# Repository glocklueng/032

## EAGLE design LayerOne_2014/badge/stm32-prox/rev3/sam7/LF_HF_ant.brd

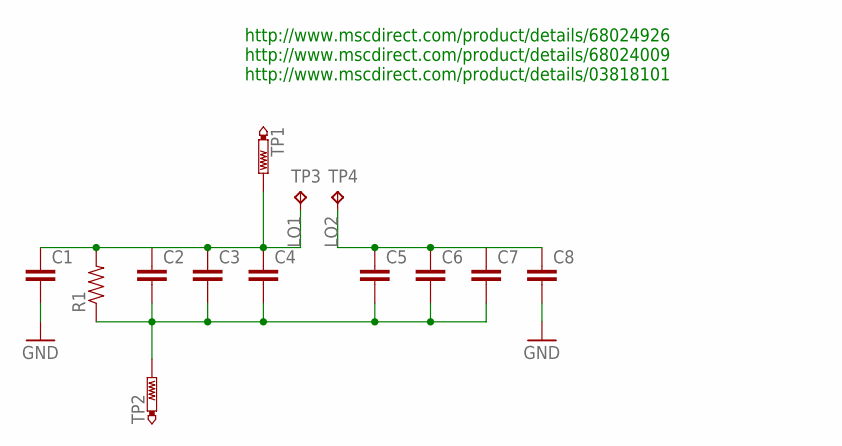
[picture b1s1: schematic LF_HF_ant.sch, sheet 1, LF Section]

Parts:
C1, C2, C3, C4, C5, C6, C7, C8: CAP1206; 1206
R1: RESISTOR0603-RES; 0603-RES
TP1, TP2: PTR1PAD1-17; P1-17
TP3, TP4: TP; TP_MILLMAX_R

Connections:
GND: C1.2, C8.2; also elsewhere on the board
LO1: C1.1, C2.1, C3.1, C4.1, R1.2, TP1.TP, TP3.TP; also elsewhere on the board
LO2: C5.1, C6.1, C7.1, C8.1, TP4.TP; also elsewhere on the board
unnamed: C2.2, C3.2, C4.2, C5.2, C6.2, C7.2, R1.1, TP2.TP

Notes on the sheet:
http://www.mscdirect.com/product/details/68024926 http://www.mscdirect.com/product/details/68024009 http://www.mscdirect.com/product/details/03818101

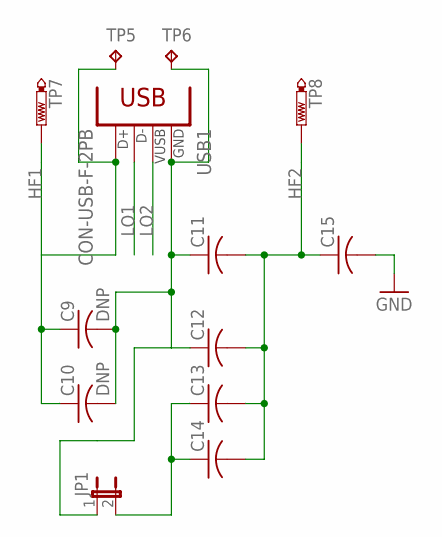
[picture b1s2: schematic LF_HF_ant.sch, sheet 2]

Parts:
C9, C10: DNP; C1206
C11, C12, C13, C14, C15: C-USC1206; C1206
JP1: JUMPER-2SMD-NO; SJ_2S-NO
TP5, TP6: TP; TP_MILLMAX_R
TP7, TP8: PTR1PAD1-17; P1-17
USB1: CON-USB-F-2PB; CONN_USB_A_F

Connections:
GND: C15.2; also elsewhere on the board
HF1: C9.1, C10.1, TP5.TP, TP7.TP, USB1.3 (D+)
HF2: C11.2, C12.2, C13.2, C14.2, C15.1, TP8.TP
LO1: USB1.2 (D-); also elsewhere on the board
LO2: USB1.1 (VUSB); also elsewhere on the board
unnamed: C9.2, C10.2, C11.1, C12.1, JP1.1, TP6.TP, USB1.4 (GND)
unnamed: C13.1, C14.1, JP1.2

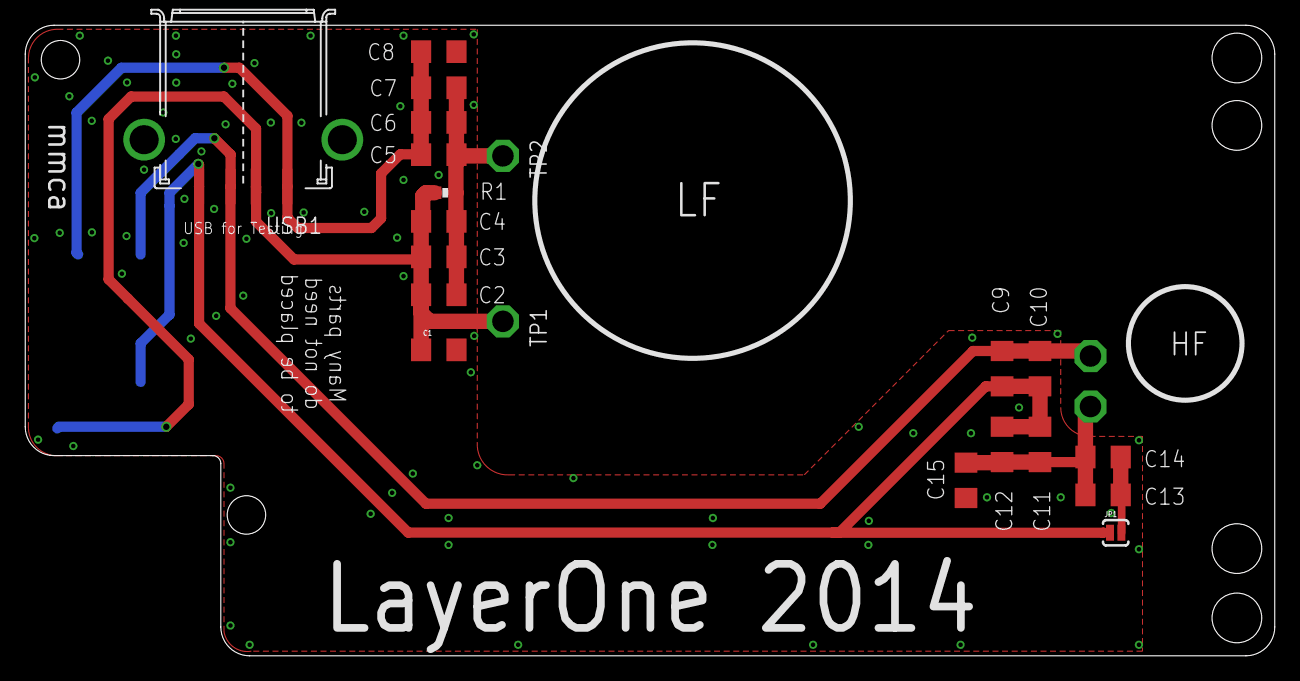
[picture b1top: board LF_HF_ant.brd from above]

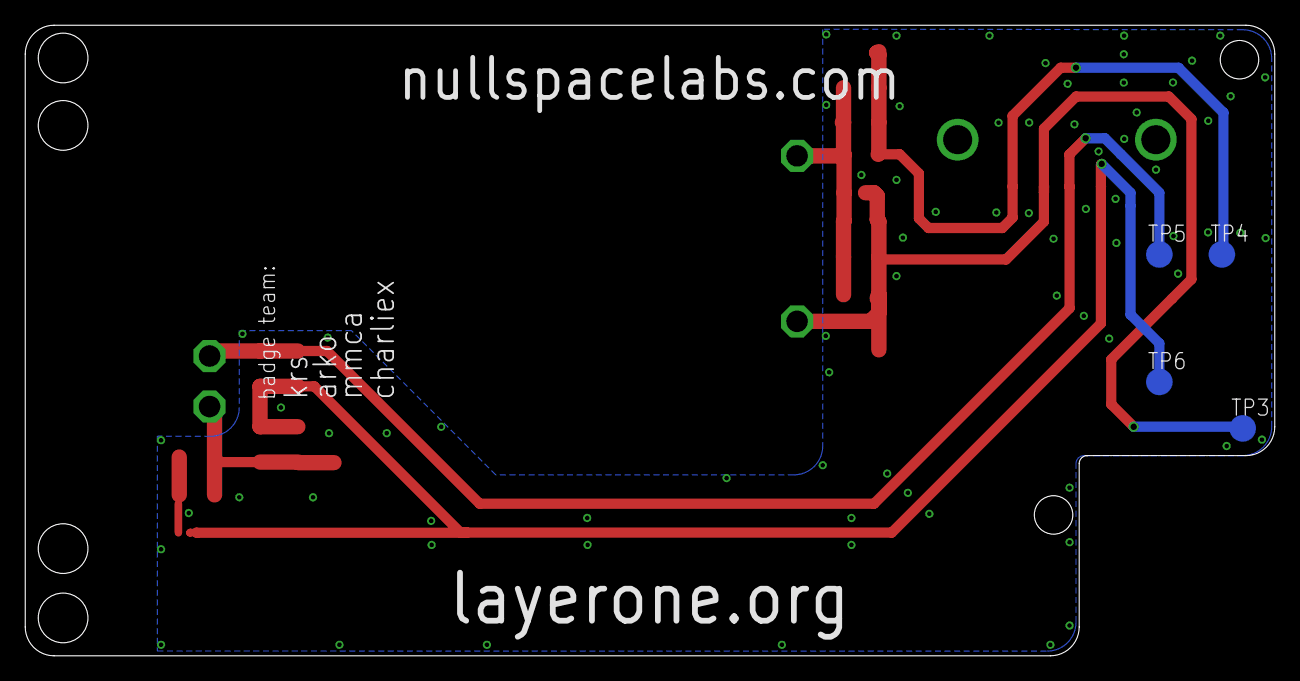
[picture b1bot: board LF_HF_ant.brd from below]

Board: 2 copper layers, 99.0 x 50.0 mm, 30 parts (5 on the bottom side), 8 nets.

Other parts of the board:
U$1, U$2: STM32-PROX_L1LOGO
U$3, U$4: STAND-OFF-TIGHT

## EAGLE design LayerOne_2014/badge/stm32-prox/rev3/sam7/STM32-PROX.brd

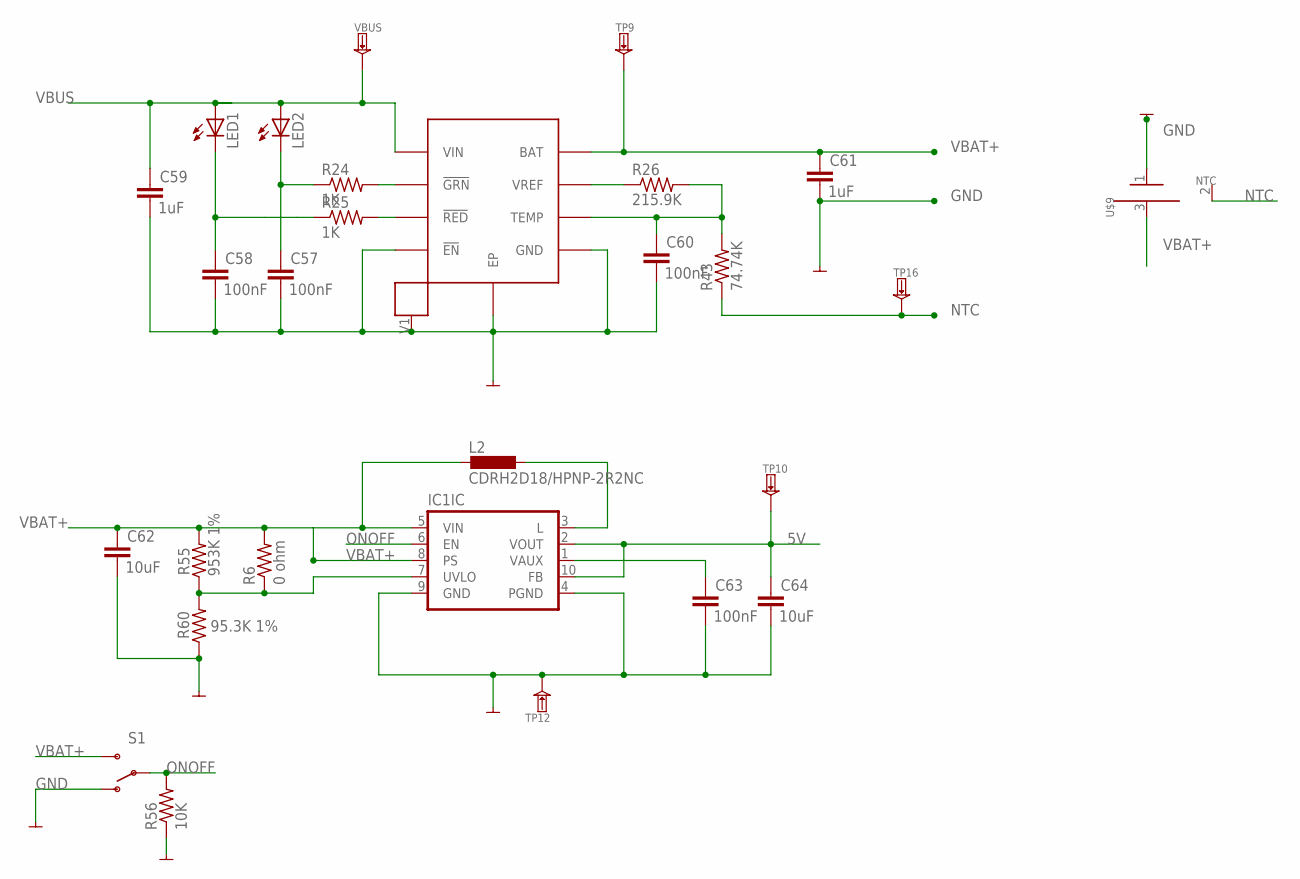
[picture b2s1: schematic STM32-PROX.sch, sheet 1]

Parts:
C57, C58, C60, C63: 100nF; RLC_0603; MPN CL10B104KO8NNNC; DIGIKEY 1276-1005-1-ND
C59, C61: 1uF; RLC_0603; MPN CC0603ZRY5V7BB105; DIGIKEY 311-1372-2-ND
C62, C64: 10uF; RLC_0603; MPN C1608X5R1C106M080AB; DIGIKEY 445-9065-1-ND
IC1: IC_TPS6120XQFN10; QFN-10; MPN TPS61202DRCT; DIGIKEY 296-21685-1-ND
L2: CDRH2D18/HPNP-2R2NC; CDRH2D18; MPN CDRH2D18/HPNP-2R2NC; DIGIKEY 308-2295-1-ND
LED1: LED_LEDSML0603; LED_SML0603; PARTNO *; DIGIKEY 475-1409-1-ND
LED2: LED_LEDSML0603; LED_SML0603; PARTNO *; DIGIKEY 475-3016-1-ND
R6: 0 ohm; RLC_0603; MPN RMCF0603JT1K00; DIGIKEY RMCF0603JT1K00TR-ND
R24, R25: 1K; RLC_0603; MPN RMCF0603JT1K00; DIGIKEY RMCF0603JT1K00TR-ND
R26: 215.9K; RLC_0603; MPN CRCW0603215KFKEA; DIGIKEY 541-215KHCT-ND
R43: 74.74K; RLC_0603; MPN RMCF0603JT75K0; DIGIKEY RMCF0603JT75K0CT-ND
R55: 953K 1%; RLC_0603; TOLERANCE 5%; MPN RC0603FR-07953KL; DIGIKEY 311-953KHRCT-ND
R56: 10K; RLC_0603; MPN RMCF0603JT1K00; DIGIKEY RMCF0603JT1K00TR-ND
R60: 95.3K 1%; RLC_0603; TOLERANCE 1%; MPN RC0603FR-0795K3L; DIGIKEY 311-95.3KHRCT-ND
S1: SWITCH-SPDT-SMD-A; SWITCH-SPST-SMD-A; PARTNO *
TP9, TP10: TESTPADKEYSTONE-SMD; --MERGED_KEYSTONE-SMD-TESTPOINT-5015; MPN NONE
TP12: TESTPADKEYSTONE-PTH; KEYSTONE-PTH-TESTPOINT-5011; MPN NONE
TP16: TESTPAD; SMD-TESTPOINT; PARTNO NONE
U$7: MC34674; UDFN-EP; MPN MC34674AEPR2; DIGIKEY MC34674AEPR2TR-ND
U$9: BATT; MPN MC34674AEPR2; DIGIKEY MC34674AEPR2TR-ND
VBUS: TESTPADKEYSTONE-PTH; KEYSTONE-PTH-TESTPOINT-5011; MPN NONE

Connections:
5V: C64.1, IC1.2 (VOUT), IC1.10 (FB), TP10.1; also elsewhere on the board
unnamed: C57.1, LED2.C, R24.1
unnamed: R24.2, U$7.2 (!GRN)
unnamed: C58.1, LED1.C, R25.1
unnamed: R25.2, U$7.3 (!RED)
unnamed: R26.1, U$7.7 (VREF)
unnamed: C60.1, R26.2, R43.2, U$7.6 (TEMP)
unnamed: C63.1, IC1.1 (VAUX)
unnamed 119: IC1.7 (UVLO), R6.1, R55.1, R60.2; also elsewhere on the board
unnamed: IC1.3 (L), L2.P$2 (2)
NTC: R43.1, TP16.1, U$9.2 (NTC)
ONOFF: IC1.6 (EN), R56.2, S1.2
VBUS: C59.1, LED1.A, LED2.A, U$7.1 (VIN), VBUS.A; also elsewhere on the board

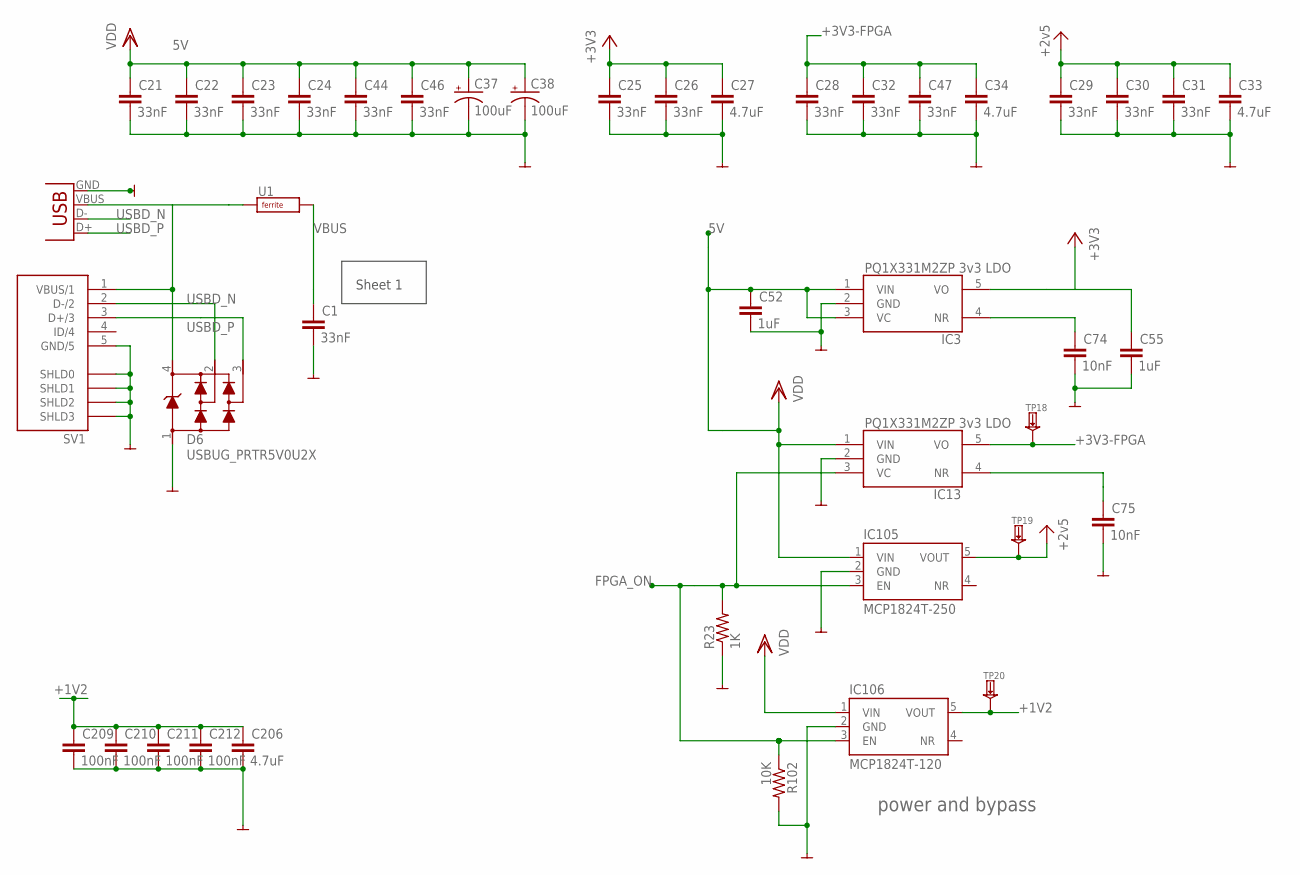
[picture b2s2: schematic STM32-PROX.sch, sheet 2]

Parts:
C1, C21, C22, C23, C24, C25, C26, C28, C29, C30, C31, C32, C44, C46, C47: 33nF; RLC_0603; MPN CC0603KRX7R9BB333; DIGIKEY 311-1429-1-ND
C27, C33, C34: 4.7uF; RLC_1210; MPN CL32B475KOINNNE; DIGIKEY 1276-1856-1-ND
C37, C38: 100uF; D/7343-31R; MPN T491D107K010AT; DIGIKEY 399-3769-1-ND
C52, C55: 1uF; RLC_0603; MPN CC0603KRX7R9BB333; DIGIKEY 311-1429-1-ND
C74, C75: 10nF; RLC_0603; MPN C0603C103K5RACTU; DIGIKEY 399-1091-2-ND
C206: 4.7uF; RLC_0603; MPN CL10A475KO8NNNC; DIGIKEY 1276-1784-2-ND
C209, C210, C211, C212: 100nF; RLC_0603; MPN CL10B104KO8NNNC; DIGIKEY 1276-1005-1-ND
D6: USBUG_PRTR5V0U2X; USBUG_SOT143B; MPN PRTR5V0U2X,215; DIGIKEY 568-4140-1-ND
IC3: PQ1X331M2ZP-3V3-LDO-SOT-23-5; SOT-23-5; MPN LP2985-33DBVR; DIGIKEY 296-18476-1-ND
IC13: PQ1X331M2ZP-3V3-LDO-SOT-23-5; SOT-23-5; MPN LP2985-33DBVR; DIGIKEY 296-18476-2-ND
IC105: MCP1824T-250; SOT-23-5; MPN MCP1824T-2502E/OT; DIGIKEY MCP1824T-2502E/OTCT-ND
IC106: MCP1824T-120; SOT-23-5; MPN MCP1824T-1202E/OT; DIGIKEY MCP1824T-1202E/OTCT-ND
R23: 1K; RLC_0603; MPN RMCF0603JT1K00; DIGIKEY RMCF0603JT1K00CT-ND
R102: 10K; RLC_0603; MPN RMCF0603JT10K0; DIGIKEY RMCF0603JT10K0CT-ND
SV1: USB-MINIB; USB-MINIB-SMD; PARTNO *
TP18, TP19, TP20: TESTPAD; SMD-TESTPOINT; PARTNO NONE
U1: FERRITE0805; RLC_0805; MPN MPZ2012S300A; DIGIKEY 445-1566-1-ND
USB-MICRO: USB-MICROB; MPN 1981568-1; DIGIKEY A97800CT-ND

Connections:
5V: C21.1, C22.1, C23.1, C24.1, C37.+, C38.+, C44.1, C46.1, C52.1, IC3.1 (VIN), IC3.3 (VC), IC13.1 (VIN), IC105.1 (VIN), IC106.1 (VIN); also elsewhere on the board
+1V2: C206.1, C209.1, C210.1, C211.1, C212.1, IC106.5 (VOUT), TP20.1; also elsewhere on the board
+2V5: C29.1, C30.1, C31.1, C33.1, IC105.5 (VOUT), TP19.1; also elsewhere on the board
+3V3-FPGA: C28.1, C32.1, C34.1, C47.1, IC13.5 (VO), TP18.1; also elsewhere on the board
FPGA_ON: IC13.3 (VC), IC105.3 (EN), IC106.3 (EN), R23.2, R102.1; also elsewhere on the board
unnamed: C74.1, IC3.4 (NR)
unnamed: C75.1, IC13.4 (NR)
USBD_N: D6.2, SV1.2 (D-/2), USB-MICRO.D-; also elsewhere on the board
USBD_P: D6.3, SV1.3 (D+/3), USB-MICRO.D+; also elsewhere on the board
VBUS: C1.1, U1.2 (B); also elsewhere on the board

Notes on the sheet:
power and bypass
Sheet 1

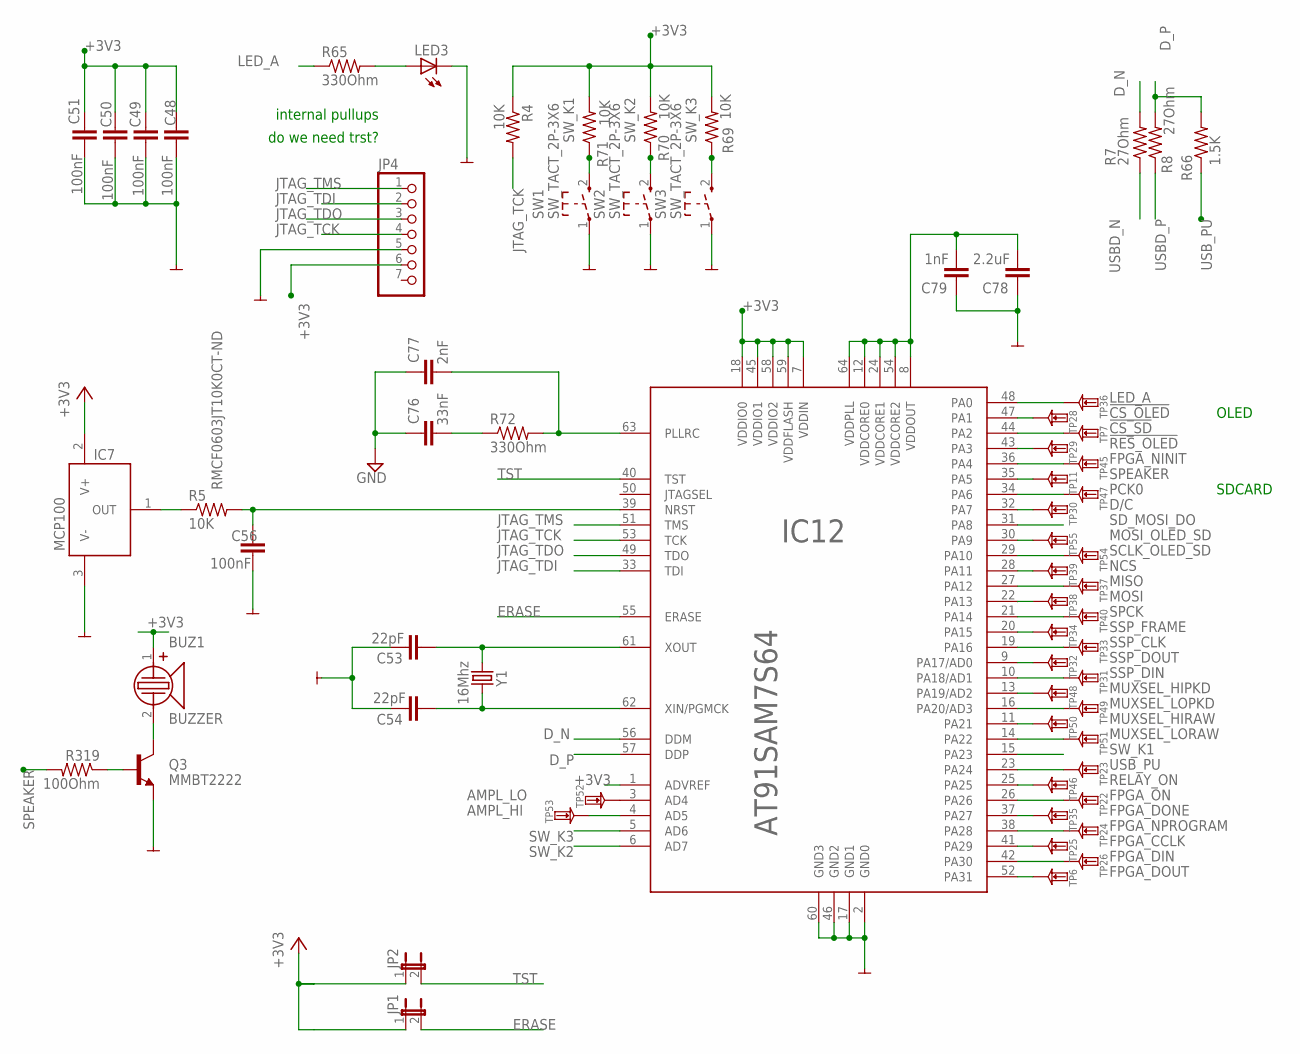
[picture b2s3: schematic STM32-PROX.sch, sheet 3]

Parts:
BUZ1: BUZZER; MPN CCV-084B16-SMT; DIGIKEY 102-1265-2-ND
C48, C49, C50, C51, C56: 100nF; RLC_0603; MPN CL10B104KO8NNNC; DIGIKEY 1276-1005-1-ND
C53, C54: 22pF; RLC_0603; MPN C1608C0G1H220J080AA; DIGIKEY 445-1273-1-ND
C76: 33nF; RLC_0603; MPN CC0603KRX7R9BB333; DIGIKEY 311-1429-1-ND
C77: 2nF; RLC_0603; MPN GRM1885C1H202JA01D; DIGIKEY 490-1458-2-ND
C78: 2.2uF; RLC_0603; MPN LMK107BJ225KA-T; DIGIKEY 587-1253-1-ND
C79: 1nF; RLC_0603; PARTNO GRM188R71H102KA01D; DIGIKEY 490-1494-2-ND
IC7: MCP100; SOT23-3LEAD; MPN MCP100T-270I/TT; DIGIKEY MCP100T-270I/TTCT-ND
IC12: AT91SAM7S512B; LQFP-64; PARTNO AT91SAM7S512B-AU; DIGIKEY AT91SAM7S512B-AU-ND
JP1, JP2: JUMPER-2PTH; 1X02
JP4: HEADER-1X7ROUND; 1X07_ROUND
LED3: LED_LEDSML0603; LED_SML0603; PARTNO *; DIGIKEY 475-2558-1-ND
Q3: MMBT2222; SOT-23-3; MPN MMBT2222A-7-F; DIGIKEY MMBT2222A-FDITR-ND
R4, R5, R69, R70, R71: 10K; RLC_0603; MPN RMCF0603JT10K0; DIGIKEY RMCF0603JT10K0CT-ND
R7, R8: 27Ohm; RLC_0603; MPN RMCF0603JT27R0; DIGIKEY RMCF0603JT27R0CT-ND
R65, R72: 330Ohm; RLC_0603; MPN RMCF0603JT330R; DIGIKEY RMCF0603JT330RCT-ND
R66: 1.5K; RLC_0603; MPN MCR03ERTJ152; DIGIKEY RHM1.5KCGTR-ND
R319: 100Ohm; RLC_0603; MPN RMCF0603JT100R; DIGIKEY RMCF0603JT100RCT-ND
SW1, SW2, SW3: SW_TACT_2P-3X6; SW_TACT_3X6
TP6, TP7, TP11, TP22, TP23, TP24, TP25, TP26, TP28, TP29, TP30, TP31, TP32, TP33, TP34, TP35, TP36, TP37, TP38, TP39, TP40, TP45, TP46, TP47, TP48, TP49, TP50, TP51, TP52, TP53, TP54, TP55: TESTPAD; SMD-TESTPOINT; PARTNO NONE
Y1: 16Mhz; CRYSTAL-TXC-7A; MPN 7A-16.000MAAJ-T; DIGIKEY 887-1086-1-ND

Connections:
!CS_OLED: IC12.47 (PA1), TP28.1; also elsewhere on the board
!CS_SD: IC12.44 (PA2), TP7.1; also elsewhere on the board
!RES_OLED: IC12.43 (PA3), TP29.1; also elsewhere on the board
AMPL_HI: IC12.4 (AD5), TP53.1; also elsewhere on the board
AMPL_LO: IC12.3 (AD4), TP52.1; also elsewhere on the board
D/C: IC12.32 (PA7), TP30.1; also elsewhere on the board
D_N: IC12.56 (DDM), R7.2
D_P: IC12.57 (DDP), R8.2, R66.2
FPGA_CCLK: IC12.41 (PA29), TP25.1; also elsewhere on the board
FPGA_DIN: IC12.42 (PA30), TP26.1; also elsewhere on the board
FPGA_DONE: IC12.37 (PA27), TP35.1; also elsewhere on the board
FPGA_DOUT: IC12.52 (PA31), TP6.1; also elsewhere on the board
FPGA_NINIT: IC12.36 (PA4), TP45.1; also elsewhere on the board
FPGA_NPROGRAM: IC12.38 (PA28), TP24.1; also elsewhere on the board
FPGA_ON: IC12.26 (PA26), TP22.1; also elsewhere on the board
JTAG_TCK: IC12.53 (TCK), JP4.4, R4.2
JTAG_TDI: IC12.33 (TDI), JP4.2
JTAG_TDO: IC12.49 (TDO), JP4.3
JTAG_TMS: IC12.51 (TMS), JP4.1
LED3: LED3.A, R65.2
LED_A: IC12.48 (PA0), R65.1, TP36.1
MISO: IC12.27 (PA12), TP37.1; also elsewhere on the board
MOSI: IC12.22 (PA13), TP38.1; also elsewhere on the board
MOSI_OLED_SD: IC12.30 (PA9), TP55.1; also elsewhere on the board
MUXSEL_HIPKD: IC12.13 (PA19/AD2), TP48.1; also elsewhere on the board
MUXSEL_HIRAW: IC12.11 (PA21), TP50.1; also elsewhere on the board
MUXSEL_LOPKD: IC12.16 (PA20/AD3), TP49.1; also elsewhere on the board
MUXSEL_LORAW: IC12.14 (PA22), TP51.1; also elsewhere on the board
unnamed: C53.2, IC12.61 (XOUT), Y1.P$1 (1)
unnamed: BUZ1.2, Q3.3 (C)
unnamed: Q3.1 (B), R319.1
unnamed: C54.2, IC12.62 (XIN/PGMCK), Y1.P$2 (2)
unnamed: IC7.1 (OUT), R5.1
unnamed: C78.2, C79.2, IC12.8 (VDDOUT), IC12.12 (VDDCORE0), IC12.24 (VDDCORE1), IC12.54 (VDDCORE2), IC12.64 (VDDPLL)
unnamed: C77.2, IC12.63 (PLLRC), R72.2
unnamed: C76.2, R72.1
NCS: IC12.28 (PA11), TP39.1; also elsewhere on the board
NRST: C56.1, IC12.39 (NRST), R5.2
unnamed: IC12.55 (ERASE), JP1.2
PCK0: IC12.34 (PA6), TP47.1; also elsewhere on the board
RELAY_ON: IC12.25 (PA25), TP46.1; also elsewhere on the board
SCLK_OLED_SD: IC12.29 (PA10), TP54.1; also elsewhere on the board
SD_MOSI_DO: IC12.31 (PA8); also elsewhere on the board
SPCK: IC12.21 (PA14), TP40.1; also elsewhere on the board
SPEAKER: IC12.35 (PA5), R319.2, TP11.1
SSP_CLK: IC12.19 (PA16), TP33.1; also elsewhere on the board
SSP_DIN: IC12.10 (PA18/AD1), TP31.1; also elsewhere on the board
SSP_DOUT: IC12.9 (PA17/AD0), TP32.1; also elsewhere on the board
SSP_FRAME: IC12.20 (PA15), TP34.1; also elsewhere on the board
SW_K1: IC12.15 (PA23), R71.1, SW1.2 (3); also elsewhere on the board
SW_K2: IC12.6 (AD7), R70.1, SW2.2 (3); also elsewhere on the board
SW_K3: IC12.5 (AD6), R69.1, SW3.2 (3); also elsewhere on the board
USBD_N: R7.1; also elsewhere on the board
USBD_P: R8.1; also elsewhere on the board
USB_PU: IC12.23 (PA24), R66.1, TP23.1

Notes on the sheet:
do we need trst?
internal pullups
OLED
SDCARD

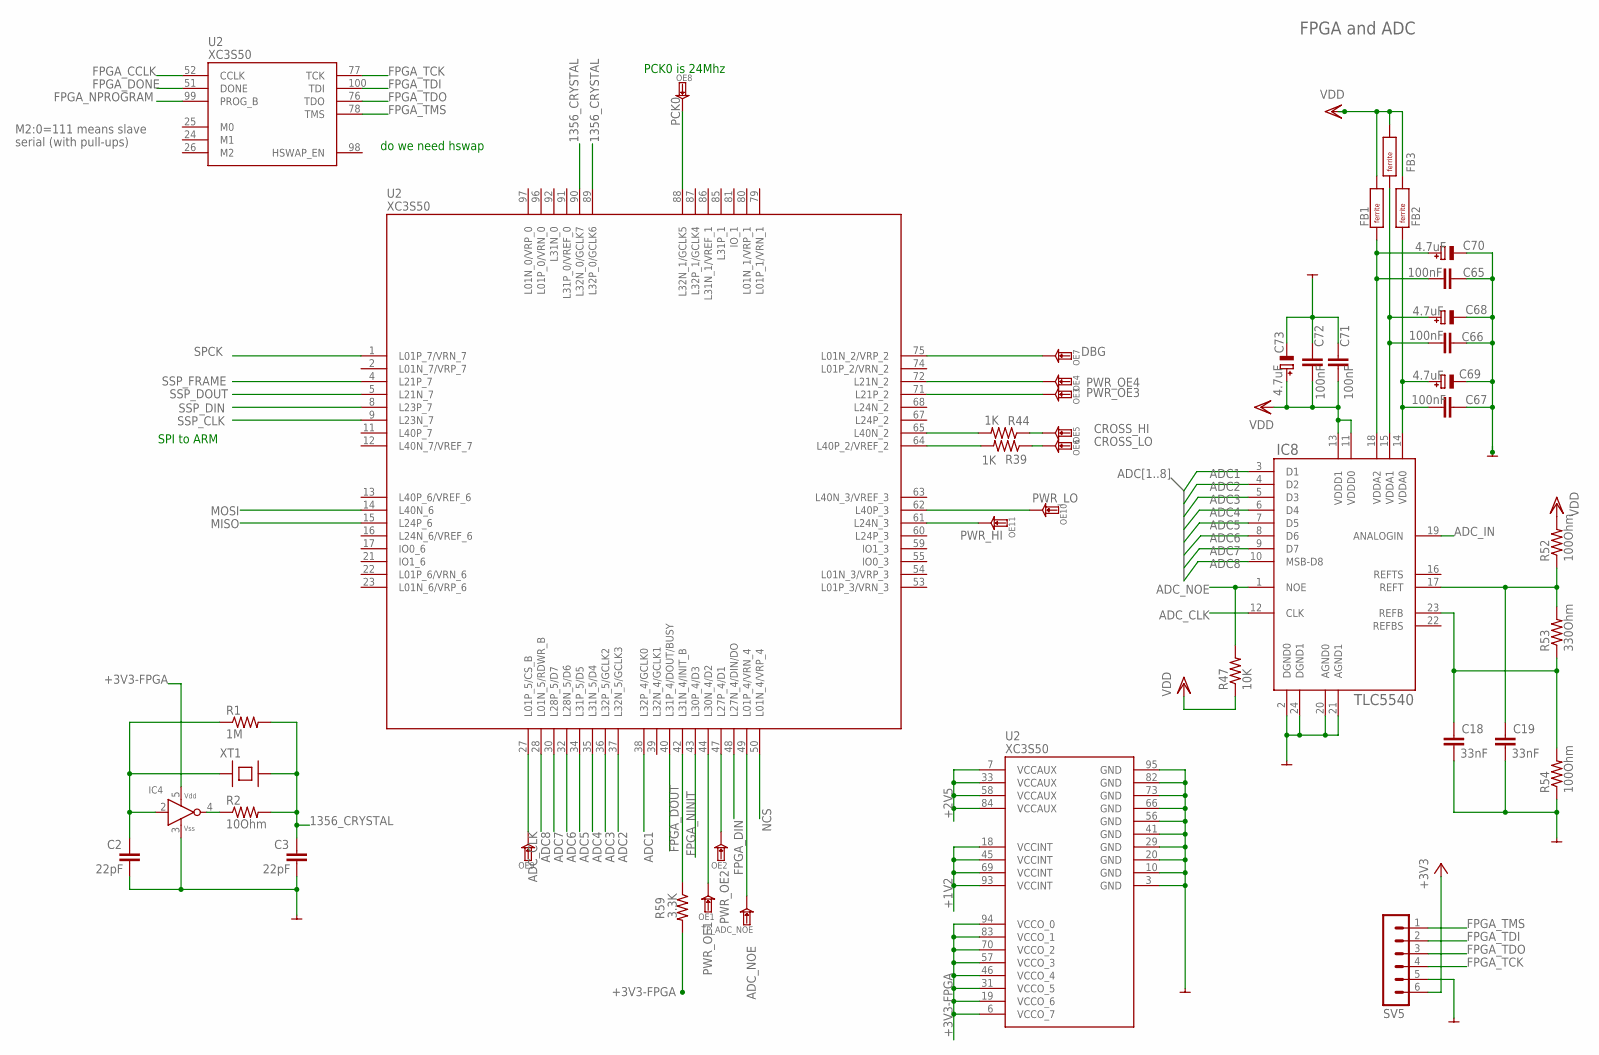
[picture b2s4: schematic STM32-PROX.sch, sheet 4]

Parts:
C2, C3: 22pF; RLC_0603; MPN C1608C0G1H220J080AA; DIGIKEY 445-1273-1-ND
C18, C19: 33nF; RLC_0603; MPN CC0603KRX7R9BB333; DIGIKEY 311-1429-1-ND
C65, C66, C67, C71, C72: 100nF; RLC_0603; MPN CL10B104KO8NNNC; DIGIKEY 1276-1005-1-ND
C68, C69, C70, C73: 4.7uF; EIA3216-18/A-R; PARTNO T491A475M010AT; DIGIKEY 399-3698-1-ND
FB1, FB2, FB3: 600 OHM; RLC_0603; PARTNO CIM10J601NC; DIGIKEY 1276-6379-2-ND
IC4: HCU-INVERTER; SMV-5; MPN NC7SZ04M5X; DIGIKEY NC7SZ04M5XCT-ND
IC8: TLC5540; TSSOP-24; MPN TLC5540IPW; DIGIKEY 296-2184-5-ND
OE1, OE2, OE3, OE4, OE5, OE6, OE7, OE8, OE9, OE10, OE11: TESTPAD; SMD-TESTPOINT; PARTNO NONE
R1: 1M; RLC_0603; MPN RC0603JR-071ML; DIGIKEY 311-1.0MGRTR-ND
R2: 10Ohm; RLC_0603; MPN RMCF0603JT100R; DIGIKEY RMCF0603JT100RCT-ND
R39, R44: 1K; RLC_0603; MPN RMCF0603JT1K00; DIGIKEY RMCF0603JT1K00CT-ND
R47: 10K; RLC_0603; MPN RMCF0603JT10K0; DIGIKEY RMCF0603JT10K0CT-ND
R52, R54: 100Ohm; RLC_0603; MPN RMCF0603JT100R; DIGIKEY RMCF0603JT100RCT-ND
R53: 330Ohm; RLC_0603; MPN RMCF0603JT330R; DIGIKEY RMCF0603JT330RCT-ND
R59: 3.3K; RLC_0603; MPN RMCF0603JT3K30; DIGIKEY RMCF0603JT3K30CT-ND
SV5: HEADER-MALE-6X1; HEADER-MALE-6X1-0.100-UNKEYED; PARTNO *
TP_ADC_NOE: TESTPAD; SMD-TESTPOINT; PARTNO NONE
U2: XC3S50; VQ100; MPN XC3S50-5VQ100C (not on bom)
XT1: XTAL-SMD-CITIZEN-CS10; MPN ABM3-13.560MHZ-B2-T; DIGIKEY 535-9101-1-ND

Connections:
5V: C71.1, C72.1, C73.+, FB1.2 (B), FB2.2 (B), FB3.2 (B), IC8.11 (VDDD0), IC8.13 (VDDD1), R47.1, R52.2; also elsewhere on the board
1356_CRYSTAL: C3.1, R1.2, R2.2, U2.89 (L32P_0/GCLK6), U2.90 (L32N_0/GCLK7), XT1.B
+1V2: U2.18 (VCCINT), U2.45 (VCCINT), U2.69 (VCCINT), U2.93 (VCCINT); also elsewhere on the board
+2V5: U2.7 (VCCAUX), U2.33 (VCCAUX), U2.58 (VCCAUX), U2.84 (VCCAUX); also elsewhere on the board
+3V3-FPGA: IC4.5 (VDD), R59.2, U2.6 (VCCO_7), U2.19 (VCCO_6), U2.31 (VCCO_5), U2.46 (VCCO_4), U2.57 (VCCO_3), U2.70 (VCCO_2), U2.83 (VCCO_1), U2.94 (VCCO_0); also elsewhere on the board
ADC1: IC8.3 (D1), U2.38 (L32P_4/GCLK0)
ADC2: IC8.4 (D2), U2.37 (L32N_5/GCLK3)
ADC3: IC8.5 (D3), U2.36 (L32P_5/GCLK2)
ADC4: IC8.6 (D4), U2.35 (L31N_5/D4)
ADC5: IC8.7 (D5), U2.34 (L31P_5/D5)
ADC6: IC8.8 (D6), U2.32 (L28N_5/D6)
ADC7: IC8.9 (D7), U2.30 (L28P_5/D7)
ADC8: IC8.10 (MSB-D8), U2.28 (L01N_5/RDWR_B)
ADC_CLK: IC8.12 (CLK), OE9.1, U2.27 (L01P_5/CS_B)
ADC_IN: IC8.19 (ANALOGIN); also elsewhere on the board
ADC_NOE: IC8.1 (NOE), R47.2, TP_ADC_NOE.1, U2.49 (L01P_4/VRN_4)
CROSS_HI: OE5.1, R44.1; also elsewhere on the board
CROSS_LO: OE6.1, R39.1; also elsewhere on the board
DBG: OE7.1, U2.75 (L01N_2/VRP_2)
FPGA_CCLK: U2.52 (CCLK); also elsewhere on the board
FPGA_DIN: U2.48 (L27N_4/DIN/DO); also elsewhere on the board
FPGA_DONE: U2.51 (DONE); also elsewhere on the board
FPGA_DOUT: U2.40 (L31P_4/DOUT/BUSY); also elsewhere on the board
FPGA_NINIT: R59.1, U2.42 (L31N_4/INIT_B); also elsewhere on the board
FPGA_NPROGRAM: U2.99 (PROG_B); also elsewhere on the board
FPGA_TCK: SV5.4, U2.77 (TCK)
FPGA_TDI: SV5.2, U2.100 (TDI)
FPGA_TDO: SV5.3, U2.76 (TDO)
FPGA_TMS: SV5.1, U2.78 (TMS)
MISO: U2.15 (L24P_6); also elsewhere on the board
MOSI: U2.14 (L40N_6); also elsewhere on the board
unnamed: IC4.4 (Y), R2.1
unnamed: C2.1, IC4.2 (A), R1.1, XT1.A
unnamed: C18.1, IC8.23 (REFB), R53.1, R54.2
unnamed: R39.2, U2.64 (L40P_2/VREF_2)
unnamed: C67.1, C69.+, FB2.1 (A), IC8.14 (VDDA0)
unnamed: C66.1, C68.+, FB3.1 (A), IC8.15 (VDDA1)
unnamed: C65.1, C70.+, FB1.1 (A), IC8.18 (VDDA2)
unnamed: R44.2, U2.65 (L40N_2)
unnamed: C19.1, IC8.17 (REFT), R52.1, R53.2
NCS: U2.50 (L01N_4/VRP_4); also elsewhere on the board
PCK0: OE8.1, U2.88 (L32N_1/GCLK5); also elsewhere on the board
PWR_HI: OE11.1, U2.61 (L24N_3); also elsewhere on the board
PWR_LO: OE10.1, U2.62 (L40P_3); also elsewhere on the board
PWR_OE1: OE1.1, U2.44 (L30N_4/D2); also elsewhere on the board
PWR_OE2: OE2.1, U2.47 (L27P_4/D1); also elsewhere on the board
PWR_OE3: OE3.1, U2.71 (L21P_2); also elsewhere on the board
PWR_OE4: OE4.1, U2.72 (L21N_2); also elsewhere on the board
SPCK: U2.1 (L01P_7/VRN_7); also elsewhere on the board
SSP_CLK: U2.9 (L23N_7); also elsewhere on the board
SSP_DIN: U2.8 (L23P_7); also elsewhere on the board
SSP_DOUT: U2.5 (L21N_7); also elsewhere on the board
SSP_FRAME: U2.4 (L21P_7); also elsewhere on the board

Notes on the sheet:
FPGA and ADC
M2:0=111 means slave
serial (with pull-ups)
do we need hswap
PCK0 is 24Mhz
SPI to ARM

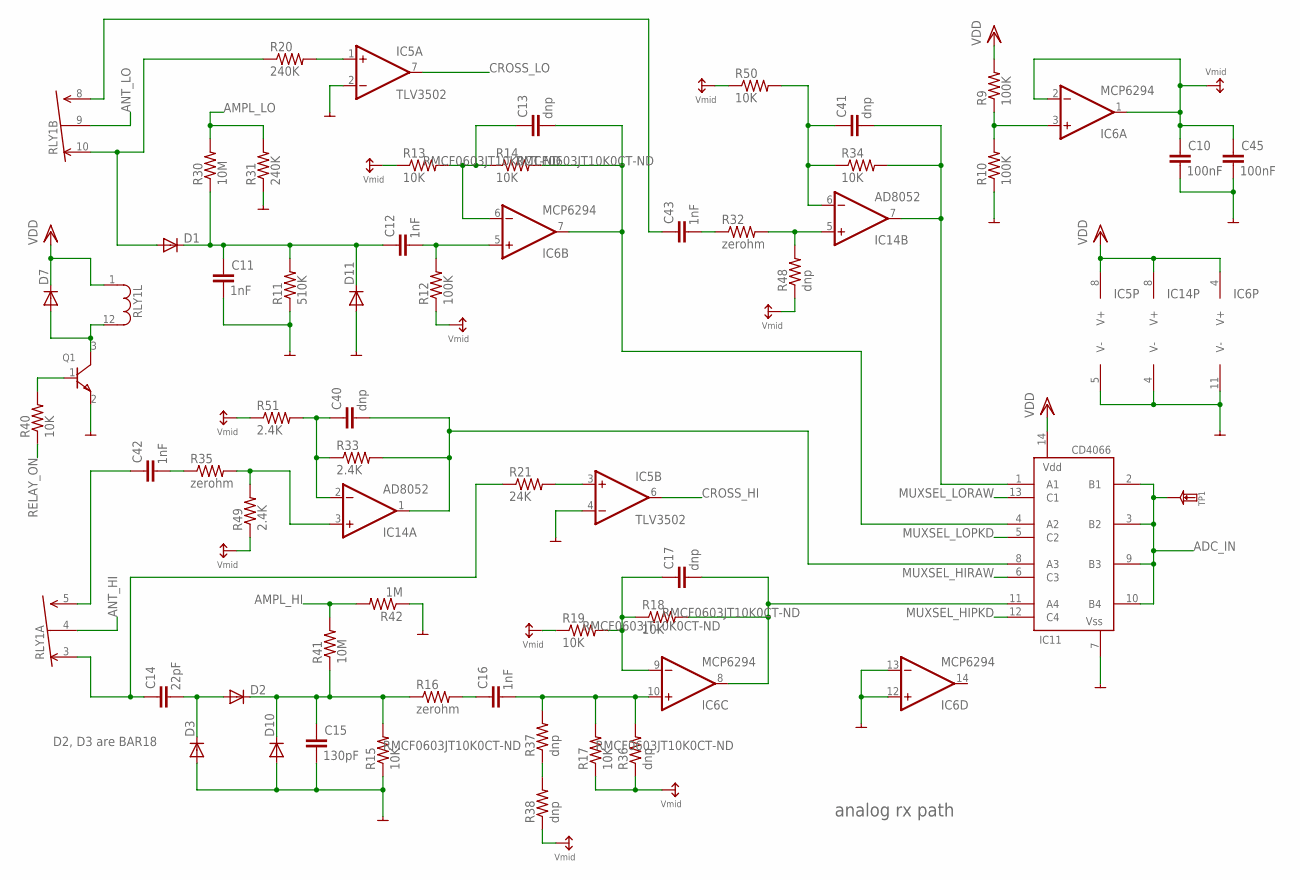
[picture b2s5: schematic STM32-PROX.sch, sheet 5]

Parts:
C10, C45: 100nF; RLC_0603; MPN CL10B104KO8NNNC; DIGIKEY 1276-1005-1-ND
C11, C12, C16, C42, C43: 1nF; RLC_0603; MPN GRM188R71H102KA01D; DIGIKEY 490-1494-2-ND
C13, C17, C40, C41: dnp; RLC_0603; PARTNO *
C14: 22pF; RLC_0603; MPN C1608C0G1H220J080AA; DIGIKEY 445-1273-1-ND
C15: 130pF; RLC_0603; MPN GRM1885C1H131JA01D; DIGIKEY 490-1430-1-ND
D1, D2, D3: DIODE-SMD-SOT23; SOT23-3LEAD; MPN BAS 21 E6327; DIGIKEY BAS21INCT-ND
D7, D10, D11: DIODE-SMD-SOT23; SOT23-3LEAD; MPN BZX84C47-7-F; DIGIKEY BZX84C47-FDICT-ND
IC5: TLV3502; SOT-23-8-OR-MSOP-8; MPN TLV3502AIDCNT; DIGIKEY 296-18147-1-ND
IC6: MCP6294; TSSOP-14; MPN MCP6294-E/ST; DIGIKEY MCP6294-E/ST-ND
IC11: CD4066; TSSOP-14; MPN CD4066BPWR; DIGIKEY 296-14123-1-ND
IC14: AD8052; MSOP8; MPN AD8052ARMZ; DIGIKEY AD8052ARMZ-ND
Q1: NPN-SOT23-2N3904; SOT23-3LEAD; MPN PMBT3904,215; DIGIKEY 568-1741-1-ND
R9, R10, R12: 100K; RLC_0603; MPN RC0603JR-07100KL; DIGIKEY 311-100KGRTR-ND
R11: 510K; RLC_0603; MPN ERJ-3GEYJ514V; DIGIKEY P510KGTR-ND
R13, R14, R15, R17, R18, R19, R34, R40, R50: 10K; RLC_0603; MPN RMCF0603JT10K0; DIGIKEY RMCF0603JT10K0CT-ND
R16, R32, R35: zerohm; RLC_0603; PARTNO *
R20, R31: 240K; RLC_0603; MPN RC1608J244CS; DIGIKEY 1276-5119-2-ND
R21: 24K; RLC_0603; MPN RC0603JR-0724KL; DIGIKEY 311-24KGRTR-ND
R30, R41: 10M; RLC_0603; MPN RC0603JR-0710ML; DIGIKEY 311-10MGRTR-ND
R33, R49, R51: 2.4K; RLC_0603; MPN RC0603FR-072K4L; DIGIKEY 311-2.40KHRTR-ND
R36, R37, R38, R48: dnp; RLC_0603; PARTNO *
R42: 1M; RLC_0603; MPN RC0603JR-071ML; DIGIKEY 311-1.0MGRTR-ND
RLY1: G6S-2H; G6S-2F; MPN G6S-2F-DC5; DIGIKEY Z888-ND
TP1: TESTPAD; SMD-TESTPOINT; PARTNO NONE

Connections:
5V: D7.3 (C), IC5.8 (V+), IC6.4 (V+), IC11.14 (VDD), IC14.8 (V+), R9.2, RLY1.1; also elsewhere on the board
ADCDR_HI: C17.2, IC6.8 (OUT), IC11.11 (A4), R18.2
ADCDR_LO: C13.2, IC6.7 (OUT), IC11.4 (A2), R14.2
ADC_IN: IC11.2 (B1), IC11.3 (B2), IC11.9 (B3), IC11.10 (B4), TP1.1; also elsewhere on the board
AMPL_HI: R41.2, R42.2; also elsewhere on the board
AMPL_LO: R30.2, R31.2; also elsewhere on the board
ANT_HI: RLY1.4 (COM); also elsewhere on the board
ANT_LO: RLY1.9 (COM); also elsewhere on the board
A_RLY_NC: C14.1, R21.1, RLY1.3 (NC)
A_RLY_NO: C42.1, RLY1.5 (NO)
B_RLY_NC: D1.1 (A), R20.1, RLY1.10 (NC)
B_RLY_NO: C43.1, RLY1.8 (NO)
CROSS_HI: IC5.6 (OUT); also elsewhere on the board
CROSS_LO: IC5.7 (OUT); also elsewhere on the board
MUXSEL_HIPKD: IC11.12 (C4); also elsewhere on the board
MUXSEL_HIRAW: IC11.6 (C3); also elsewhere on the board
MUXSEL_LOPKD: IC11.5 (C2); also elsewhere on the board
MUXSEL_LORAW: IC11.13 (C1); also elsewhere on the board
unnamed: IC6.3 (+IN), R9.1, R10.2
unnamed: C17.1, IC6.9 (-IN), R18.1, R19.2
unnamed: C12.2, IC6.5 (+IN), R12.2
unnamed: C13.1, IC6.6 (-IN), R13.2, R14.1
unnamed: C16.1, R16.2
unnamed: C11.1, C12.1, D1.3 (C), D11.3 (C), R11.2, R30.1
unnamed: C14.2, D2.1 (A), D3.3 (C)
unnamed: C15.1, D2.3 (C), D10.3 (C), R15.2, R16.1, R41.1
unnamed: C16.2, IC6.10 (+IN), R17.2, R36.2, R37.2
unnamed: IC5.1 (+IN), R20.2
unnamed: IC5.3 (+IN), R21.2
unnamed: D7.1 (A), Q1.3 (C), RLY1.12
unnamed: Q1.1 (B), R40.2
unnamed: C41.2, IC11.1 (A1), IC14.7 (OUT), R34.2
unnamed: IC14.3 (+IN), R35.2, R49.2
unnamed: C43.2, R32.1
unnamed: C42.2, R35.1
unnamed: C40.1, IC14.2 (-IN), R33.1, R51.2
unnamed: C41.1, IC14.6 (-IN), R34.1, R50.2
unnamed: IC14.5 (+IN), R32.2, R48.2
unnamed: R37.1, R38.2
RAW_HI: C40.2, IC11.8 (A3), IC14.1 (OUT), R33.2
RELAY_ON: R40.1; also elsewhere on the board
VMID: C10.1, C45.1, IC6.1 (OUT), IC6.2 (-IN), R12.1, R13.1, R17.1, R19.1, R36.1, R38.1, R48.1, R49.1, R50.1, R51.1

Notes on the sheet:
analog rx path
D2, D3 are BAR18

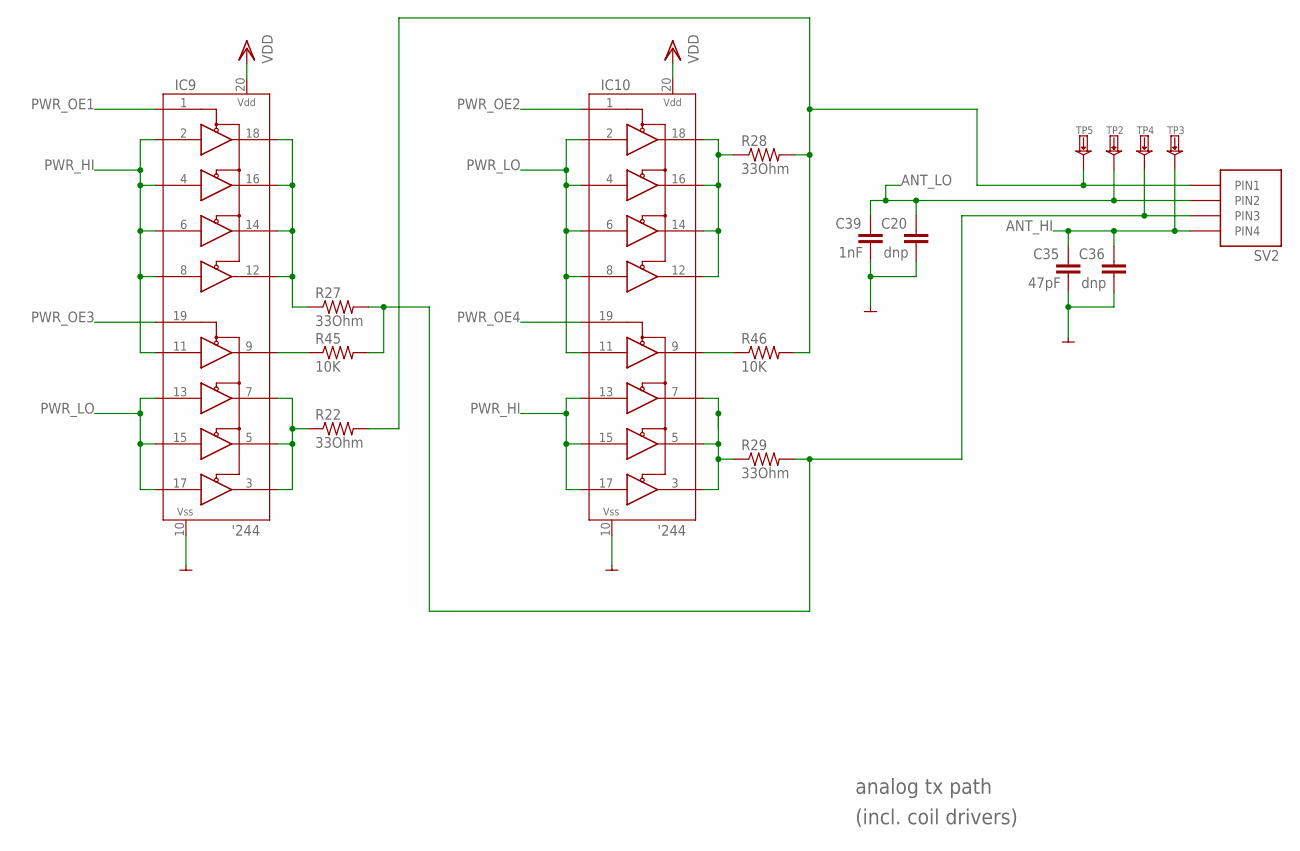
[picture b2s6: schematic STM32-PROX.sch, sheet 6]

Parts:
C20, C36: dnp; RLC_0603; PARTNO *
C35: 47pF; RLC_0603; MPN CL10C470JB8NNNC; DIGIKEY 1276-1037-1-ND
C39: 1nF; RLC_0603; MPN GRM188R71H102KA01D; DIGIKEY 490-1494-2-ND
IC9, IC10: 74XX244; TSSOP-20; MPN 74AC244TTR; DIGIKEY 497-2913-1-ND
R22, R27, R28, R29: 33Ohm; RLC_0603; MPN RC0603JR-0733RL; DIGIKEY 311-33GRTR-ND
R45, R46: 10K; RLC_0603; MPN RMCF0603JT10K0; DIGIKEY RMCF0603JT10K0CT-ND
SV2: HIROSE-MQ172-4POS; MPN MQ172X-4PA(66); DIGIKEY H10488CT-ND
TP2, TP3, TP4, TP5: TESTPADKEYSTONE-SMD; KEYSTONE-SMD-TESTPOINT-5015; PARTNO NONE

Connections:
5V: IC9.20 (VDD), IC10.20 (VDD); also elsewhere on the board
ANT_HI: C35.1, C36.1, SV2.4 (PIN4), TP3.1; also elsewhere on the board
ANT_LO: C20.1, C39.1, SV2.2 (PIN2), TP2.1; also elsewhere on the board
unnamed: R27.2, R29.2, R45.2, SV2.3 (PIN3), TP4.1
unnamed: R22.2, R28.2, R46.2, SV2.1 (PIN1), TP5.1
unnamed: IC9.12 (1Y4), IC9.14 (1Y3), IC9.16 (1Y2), IC9.18 (1Y1), R27.1
unnamed: IC10.12 (1Y4), IC10.14 (1Y3), IC10.16 (1Y2), IC10.18 (1Y1), R28.1
unnamed: IC9.3 (2Y4), IC9.5 (2Y3), IC9.7 (2Y2), R22.1
unnamed: IC10.3 (2Y4), IC10.5 (2Y3), IC10.7 (2Y2), R29.1
unnamed: IC9.9 (2Y1), R45.1
unnamed: IC10.9 (2Y1), R46.1
PWR_HI: IC9.2 (1A1), IC9.4 (1A2), IC9.6 (1A3), IC9.8 (1A4), IC9.11 (2A1), IC10.13 (2A2), IC10.15 (2A3), IC10.17 (2A4); also elsewhere on the board
PWR_LO: IC9.13 (2A2), IC9.15 (2A3), IC9.17 (2A4), IC10.2 (1A1), IC10.4 (1A2), IC10.6 (1A3), IC10.8 (1A4), IC10.11 (2A1); also elsewhere on the board
PWR_OE1: IC9.1 (1NOE); also elsewhere on the board
PWR_OE2: IC10.1 (1NOE); also elsewhere on the board
PWR_OE3: IC9.19 (2NOE); also elsewhere on the board
PWR_OE4: IC10.19 (2NOE); also elsewhere on the board

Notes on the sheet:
analog tx path
(incl. coil drivers)

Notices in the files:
LayerOne_2015/Badge/eagle/dock/vocore_dock.brd:
copyright © 2014 vonger.cn
parts and their libraries:
microbuilder: This work is placed in the public domain, and may be freely used for commercial and non-commercial work with the following conditions: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
SparkFun-Passives: Licensing: CC v3.0 Share-Alike You are welcome to use this library for commercial purposes.
